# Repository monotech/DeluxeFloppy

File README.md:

Monotech DeluxeFloppy
----

Schematic is based on Sergey Kiselev's (https://github.com/skiselev) design: http://www.malinov.com/Home/sergeys-projects/isa-fdc-and-uart

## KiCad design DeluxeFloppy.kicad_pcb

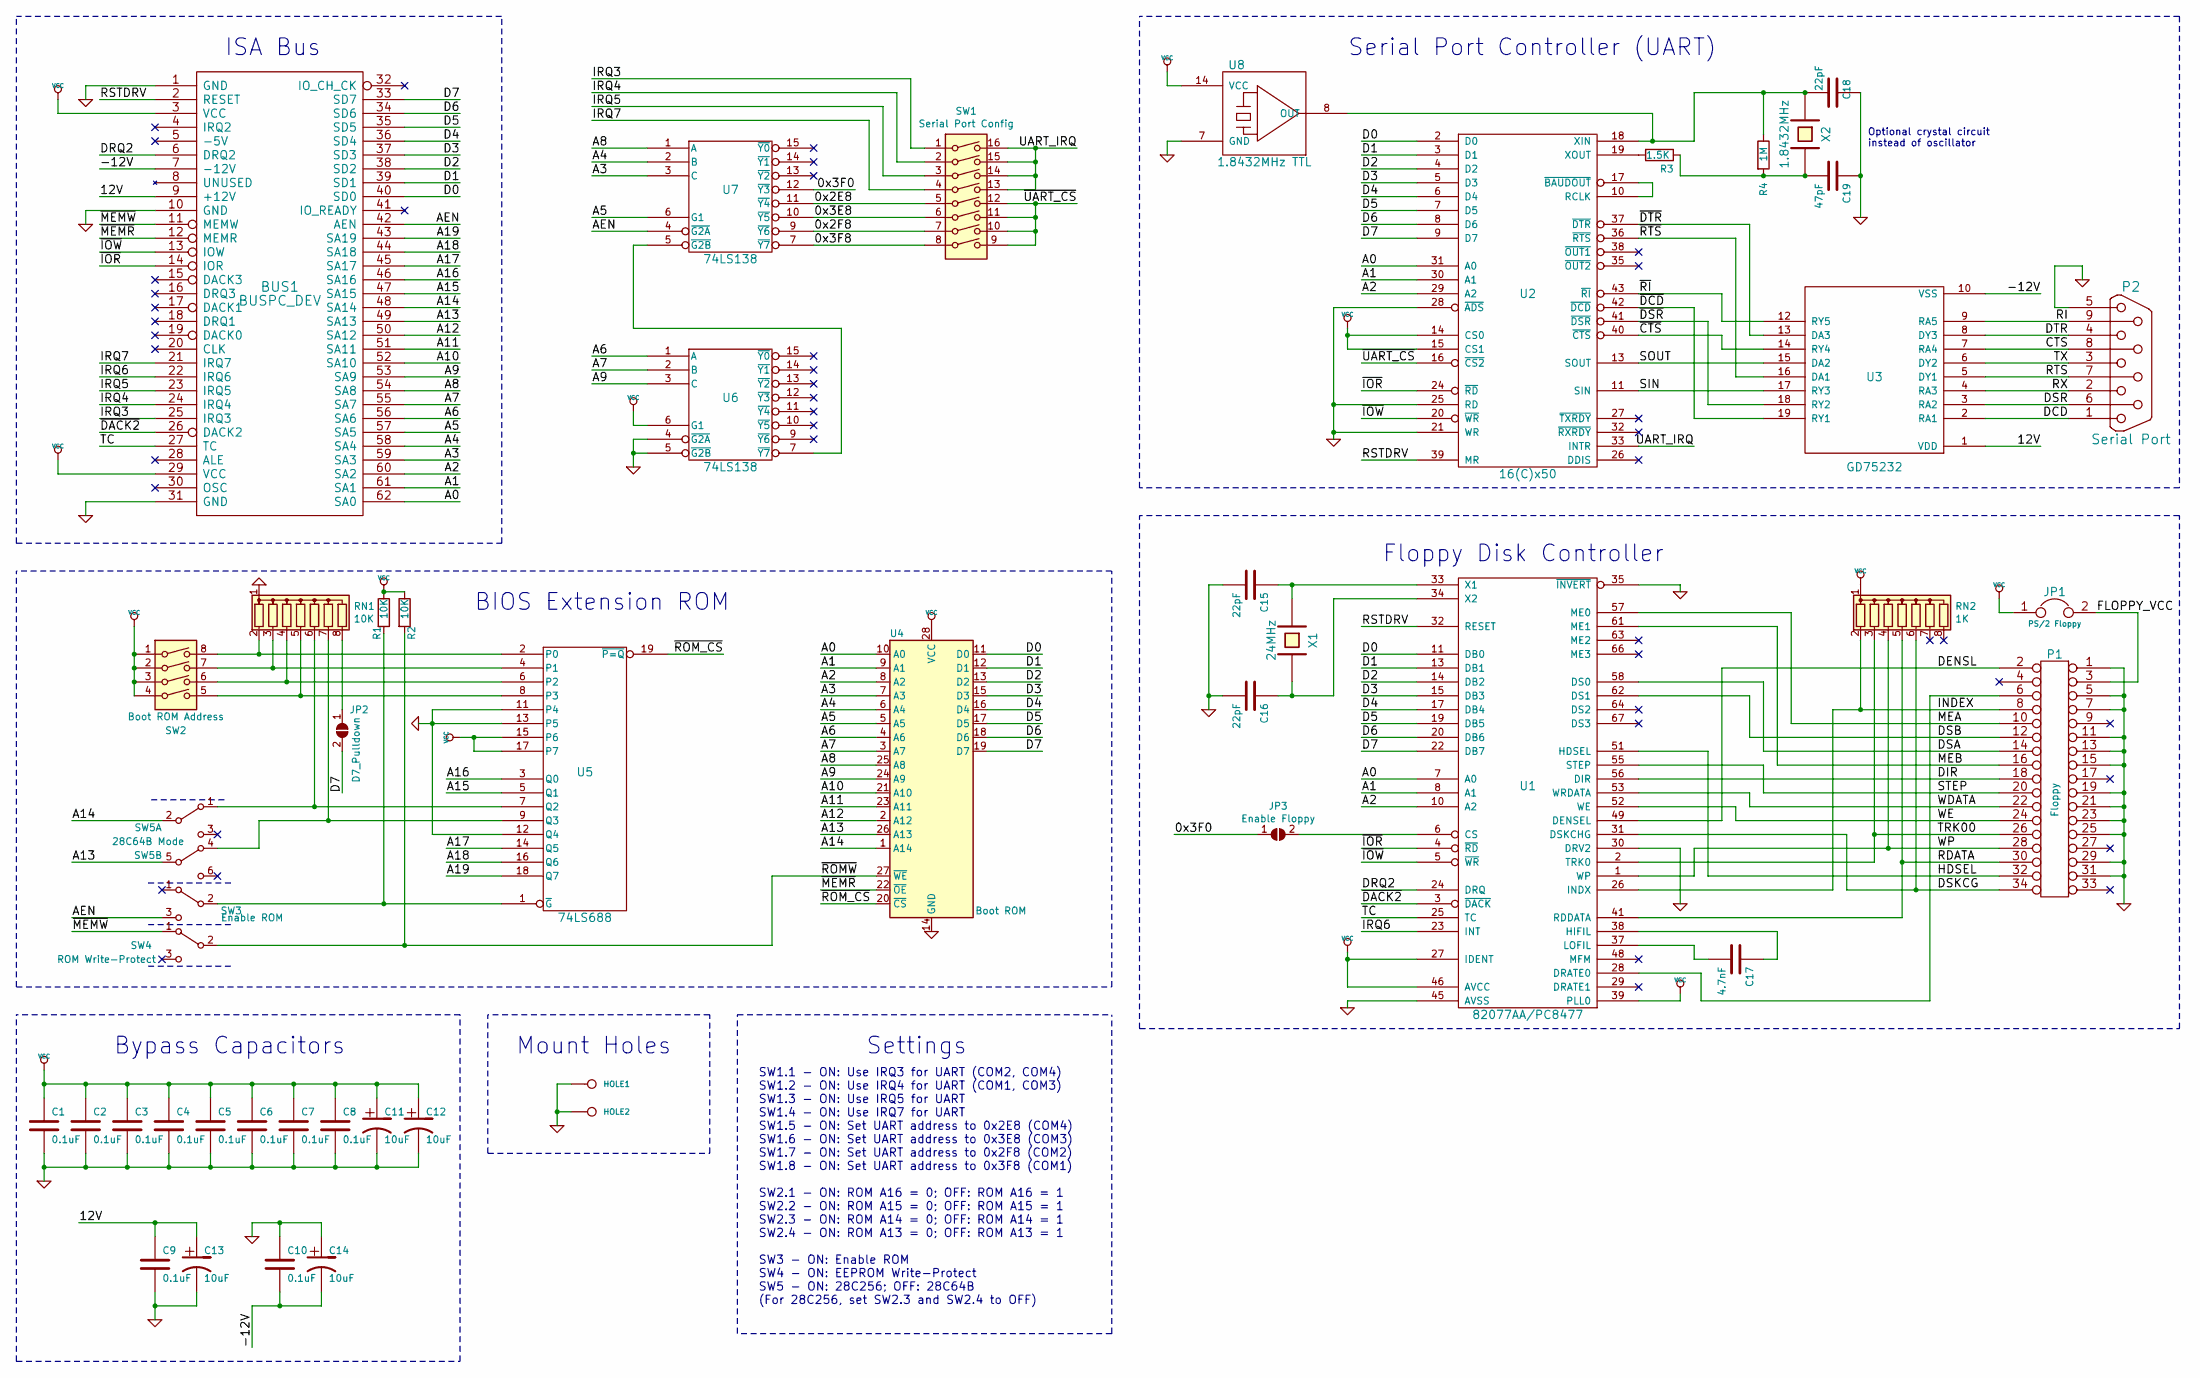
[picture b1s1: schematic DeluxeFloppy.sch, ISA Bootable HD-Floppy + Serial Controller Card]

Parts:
BUS1: BUSPC_DEV; Conn_Bus_ISA8
C1, C2, C3, C4, C5, C6, C7, C8, C9, C10: 0.1uF; C_Disc_D4.3mm_W1.9mm_P5.00mm
C11, C12, C13, C14: 10uF; C_Disc_D4.3mm_W1.9mm_P5.00mm
C15, C16, C18: 22pF; C_Disc_D4.3mm_W1.9mm_P5.00mm
C17: 4.7nF; C_Disc_D4.3mm_W1.9mm_P5.00mm
C19: 47pF; C_Disc_D4.3mm_W1.9mm_P5.00mm
HOLE1, HOLE2: CONN_1; MountingHole_3.2mm_M3_Pad
JP1: PS/2 Floppy; PinHeader_1x02_P2.54mm_Vertical
JP2: D7_Pulldown; SolderJumper-2_P1.3mm_Open_RoundedPad1.0x1.5mm
JP3: Enable Floppy; SolderJumper-2_P1.3mm_Open_RoundedPad1.0x1.5mm
P1: Floppy; Pin_Header_Straight_2x17_Pitch2.54mm_shrouded
P2: Serial Port; Conn_Dsub_DE9M
R1, R2: 10K; R_Axial_DIN0207_L6.3mm_D2.5mm_P7.62mm_Horizontal
R3: 1.5K; R_Axial_DIN0207_L6.3mm_D2.5mm_P7.62mm_Horizontal
R4: 1M; R_Axial_DIN0207_L6.3mm_D2.5mm_P7.62mm_Horizontal
RN1: 10K; R_Array_SIP8
RN2: 1K; R_Array_SIP8
SW1: Serial Port Config; SW_DIP_SPSTx08_Slide_9.78x22.5mm_W7.62mm_P2.54mm
SW2: Boot ROM Address; SW_DIP_SPSTx04_Slide_9.78x12.34mm_W7.62mm_P2.54mm
SW3: Enable ROM; SW_CuK_OS102011MA1QN1_SPDT_Angled
SW4: ROM Write-Protect; SW_CuK_OS102011MA1QN1_SPDT_Angled
SW5: 28C64B Mode; SW_MS-22D18G2
U1: 82077AA/PC8477; PLCC-68_THT-Socket
U2: 16(C)x50; PLCC-44_THT-Socket
U3: GD75232; SSOP-20_5.3x7.2mm_P0.65mm
U4: Boot ROM; DIP-28_W15.24mm_Socket
U5: 74LS688; DIP-20_W7.62mm
U6, U7: 74LS138; DIP-16_W7.62mm
U8: 1.8432MHz TTL; Oscillator_DIP-14
X1: 24MHz; Crystal_HC49-4H_Vertical
X2: 1.8432MHz; Crystal_HC49-U_Horizontal_1EP_style2

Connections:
/0x2E8: SW1.5, U7.11 (~Y4)
/0x2F8: SW1.7, U7.9 (~Y6)
/0x3E8: SW1.6, U7.10 (~Y5)
/0x3F0: JP3.1 (A), U7.12 (~Y3)
/0x3F8: SW1.8, U7.7 (~Y7)
/12V: BUS1.9 (+12V), C9.1, C13.1, U3.1 (VDD)
/-12V: BUS1.7 (-12V), C10.2, C14.2, U3.10 (VSS)
/A0: BUS1.62 (SA0), U1.7 (A0), U2.31 (A0), U4.10 (A0)
/A1: BUS1.61 (SA1), U1.8 (A1), U2.30 (A1), U4.9 (A1)
/A2: BUS1.60 (SA2), U1.10 (A2), U2.29 (A2), U4.8 (A2)
/A3: BUS1.59 (SA3), U4.7 (A3), U7.3 (C)
/A4: BUS1.58 (SA4), U4.6 (A4), U7.2 (B)
/A5: BUS1.57 (SA5), U4.5 (A5), U7.6 (G1)
/A6: BUS1.56 (SA6), U4.4 (A6), U6.1 (A)
/A7: BUS1.55 (SA7), U4.3 (A7), U6.2 (B)
/A8: BUS1.54 (SA8), U4.25 (A8), U7.1 (A)
/A9: BUS1.53 (SA9), U4.24 (A9), U6.3 (C)
/A10: BUS1.52 (SA10), U4.21 (A10)
/A11: BUS1.51 (SA11), U4.23 (A11)
/A12: BUS1.50 (SA12), U4.2 (A12)
/A13: BUS1.49 (SA13), SW5.5 (B), U4.26 (A13)
/A14: BUS1.48 (SA14), SW5.2 (B), U4.1 (A14)
/A15: BUS1.47 (SA15), U5.5 (Q1)
/A16: BUS1.46 (SA16), U5.3 (Q0)
/A17: BUS1.45 (SA17), U5.14 (Q5)
/A18: BUS1.44 (SA18), U5.16 (Q6)
/A19: BUS1.43 (SA19), U5.18 (Q7)
/AEN: BUS1.42 (AEN), SW3.3 (C), U7.4 (~G2A)
/CTS: P2.8, U3.7 (RA4)
/D0: BUS1.40 (SD0), U1.11 (DB0), U2.2 (D0), U4.11 (D0)
/D1: BUS1.39 (SD1), U1.13 (DB1), U2.3 (D1), U4.12 (D1)
/D2: BUS1.38 (SD2), U1.14 (DB2), U2.4 (D2), U4.13 (D2)
/D3: BUS1.37 (SD3), U1.15 (DB3), U2.5 (D3), U4.15 (D3)
/D4: BUS1.36 (SD4), U1.17 (DB4), U2.6 (D4), U4.16 (D4)
/D5: BUS1.35 (SD5), U1.19 (DB5), U2.7 (D5), U4.17 (D5)
/D6: BUS1.34 (SD6), U1.20 (DB6), U2.8 (D6), U4.18 (D6)
/D7: BUS1.33 (SD7), JP2.2 (B), U1.22 (DB7), U2.9 (D7), U4.19 (D7)
/DCD: P2.1, U3.2 (RA1)
/DENSL: P1.2, U1.49 (DENSEL)
/DIR: P1.18, U1.56 (DIR)
/DRQ2: BUS1.6 (DRQ2), U1.24 (DRQ)
/DSA: P1.14, U1.58 (DS0)
/DSB: P1.12, U1.62 (DS1)
/DSKCG: P1.34, RN2.6 (R5), U1.31 (DSKCHG)
/DSR: P2.6, U3.3 (RA2)
/DTR: P2.4, U3.8 (DY3)
/FLOPPY_VCC: JP1.2, P1.3
/HDSEL: P1.32, U1.51 (HDSEL)
/INDEX: P1.8, RN2.2 (R1), U1.26 (INDX)
/IRQ3: BUS1.25 (IRQ3), SW1.1
/IRQ4: BUS1.24 (IRQ4), SW1.2
/IRQ5: BUS1.23 (IRQ5), SW1.3
/IRQ6: BUS1.22 (IRQ6), U1.23 (INT)
/IRQ7: BUS1.21 (IRQ7), SW1.4
/MEA: P1.10, U1.57 (ME0)
/MEB: P1.16, U1.61 (ME1)
/RDATA: P1.30, RN2.5 (R4), U1.41 (RDDATA)
/RI: P2.9, U3.9 (RA5)
/RSTDRV: BUS1.2 (RESET), U1.32 (RESET), U2.39 (MR)
/RTS: P2.7, U3.5 (DY1)
/RX: P2.2, U3.4 (RA3)
/SIN: U2.11 (SIN), U3.17 (RY3)
/SOUT: U2.13 (SOUT), U3.15 (DA2)
/STEP: P1.20, U1.55 (STEP)
/TC: BUS1.27 (TC), U1.25 (TC)
/TRK00: P1.26, RN2.3 (R2), U1.2 (TRK0)
/TX: P2.3, U3.6 (DY2)
/UART_IRQ: SW1.13, SW1.14, SW1.15, SW1.16, U2.33 (INTR)
/WDATA: P1.22, U1.53 (WRDATA)
/WE: P1.24, U1.52 (WE)
/WP: P1.28, RN2.4 (R3), U1.1 (WP)
/~CTS: U2.40 (~CTS), U3.14 (RY4)
/~DACK2: BUS1.26 (DACK2), U1.3 (~DACK)
/~DCD: U2.42 (~DCD), U3.19 (RY1)
/~DSR: U2.41 (~DSR), U3.18 (RY2)
/~DTR: U2.37 (~DTR), U3.13 (DA3)
/~IOR: BUS1.14 (IOR), U1.4 (~RD), U2.24 (~RD)
/~IOW: BUS1.13 (IOW), U1.5 (~WR), U2.20 (~WR)
/~MEMR: BUS1.12 (MEMR), U4.22 (~OE)
/~MEMW: BUS1.11 (MEMW), SW4.1 (A)
/~RI: U2.43 (~RI), U3.12 (RY5)
/~ROMW: R2.2, SW4.2 (B), U4.27 (~WE)
/~ROM_CS: U4.20 (~CS), U5.19 (~P=Q)
/~RTS: U2.36 (~RTS), U3.16 (DA1)
/~UART_CS: SW1.9, SW1.10, SW1.11, SW1.12, U2.16 (~CS2)
GND: BUS1.1 (GND), BUS1.10 (GND), BUS1.31 (GND), C1.2, C2.2, C3.2, C4.2, C5.2, C6.2, C7.2, C8.2, C9.2, C10.1, C11.2, C12.2, C13.2, C14.1, C15.2, C16.2, C18.1, C19.1, HOLE1.1, HOLE2.1, P1.1, P1.5, P1.7, P1.11, P1.13, P1.15, P1.19, P1.21, P1.23, P1.25, P1.29, P1.31, P2.5, RN1.1 (common), U1.9 (GND), U1.12 (GND), U1.16 (GND), U1.21 (GND), U1.30 (DRV2), U1.35 (~INVERT), U1.36 (GND), U1.45 (AVSS), U1.50 (GND), U1.54 (GND), U1.59 (GND), U1.65 (GND), U2.21 (WR), U2.22 (GND), U2.25 (RD), U2.28 (~ADS), U3.11 (GND), U4.14 (GND), U5.10 (GND), U5.11 (P4), U5.12 (Q4), U5.13 (P5), U6.4 (~G2A), U6.5 (~G2B), U6.8 (GND), U7.8 (GND), U8.7 (GND)
unnamed: C15.1, U1.33 (X1), X1.1
unnamed: C16.1, U1.34 (X2), X1.2
unnamed: C17.1, U1.38 (HIFIL)
unnamed: C17.2, U1.37 (LOFIL)
unnamed: C18.2, R4.1, U2.18 (XIN), U8.8 (OUT), X2.1
unnamed: C19.2, R3.1, R4.2, X2.2
unnamed: JP2.1 (A), RN1.8 (R7)
unnamed: JP3.2 (B), U1.6 (CS)
unnamed: P1.6, U1.28 (DRATE0)
unnamed: R1.2, SW3.2 (B), U5.1 (~G)
unnamed: R3.2, U2.19 (XOUT)
unnamed: RN1.2 (R1), SW2.8, U5.2 (P0)
unnamed: RN1.3 (R2), SW2.7, U5.4 (P1)
unnamed: RN1.4 (R3), SW2.6, U5.6 (P2)
unnamed: RN1.5 (R4), SW2.5, U5.8 (P3)
unnamed: RN1.6 (R5), SW5.1 (A), U5.7 (Q2)
unnamed: RN1.7 (R6), SW5.4 (A), U5.9 (Q3)
unnamed: U2.10 (RCLK), U2.17 (~BAUDOUT)
unnamed: U6.7 (~Y7), U7.5 (~G2B)
VCC: BUS1.3 (VCC), BUS1.29 (VCC), C1.1, C2.1, C3.1, C4.1, C5.1, C6.1, C7.1, C8.1, C11.1, C12.1, JP1.1, R1.1, R2.1, RN2.1 (common), SW2.1, SW2.2, SW2.3, SW2.4, U1.18 (VCC), U1.27 (IDENT), U1.39 (PLL0), U1.40 (VCC), U1.46 (AVCC), U1.60 (VCC), U1.68 (VCC), U2.14 (CS0), U2.15 (CS1), U2.44 (VCC), U3.20 (VCC), U4.28 (VCC), U5.15 (P6), U5.17 (P7), U5.20 (VCC), U6.6 (G1), U6.16 (VCC), U7.16 (VCC), U8.14 (VCC)

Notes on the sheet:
ISA Bus
BIOS Extension ROM
Bypass Capacitors
Mount Holes
Serial Port Controller (UART)
Floppy Disk Controller
SW1.1 - ON: Use IRQ3 for UART (COM2, COM4) SW1.2 - ON: Use IRQ4 for UART (COM1, COM3) SW1.3 - ON: Use IRQ5 for UART SW1.4 - ON: Use IRQ7 for UART SW1.5 - ON: Set UART address to 0x2E8 (COM4) SW1.6 - ON: Set UART address to 0x3E8 (COM3) SW1.7 - ON: Set UART address to 0x2F8 (COM2) SW1.8 - ON: Set UA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
Settings
Optional crystal circuit instead of oscillator

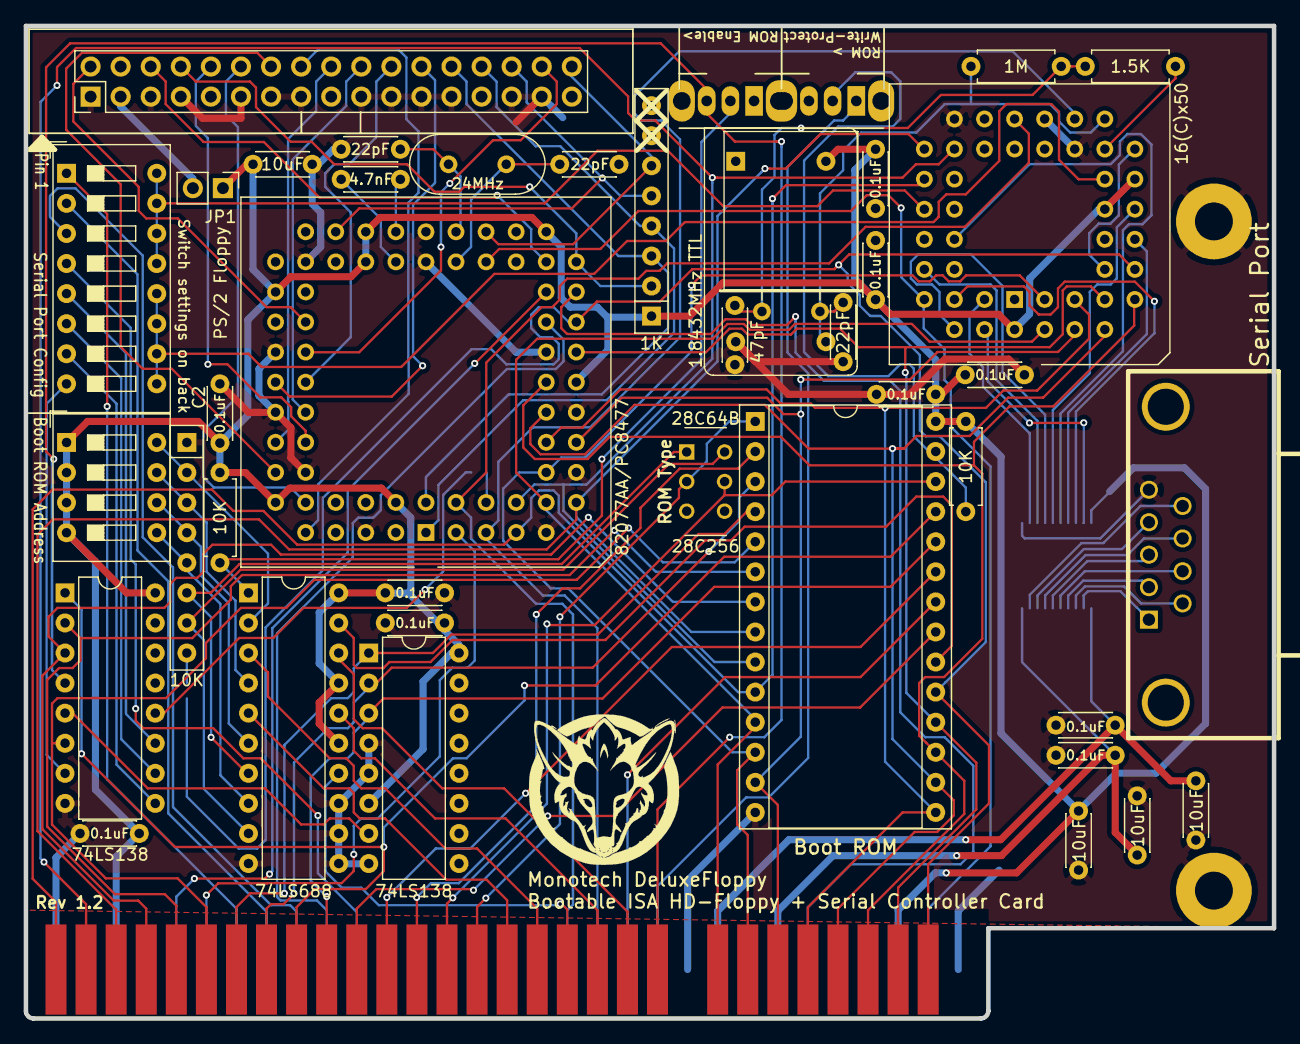
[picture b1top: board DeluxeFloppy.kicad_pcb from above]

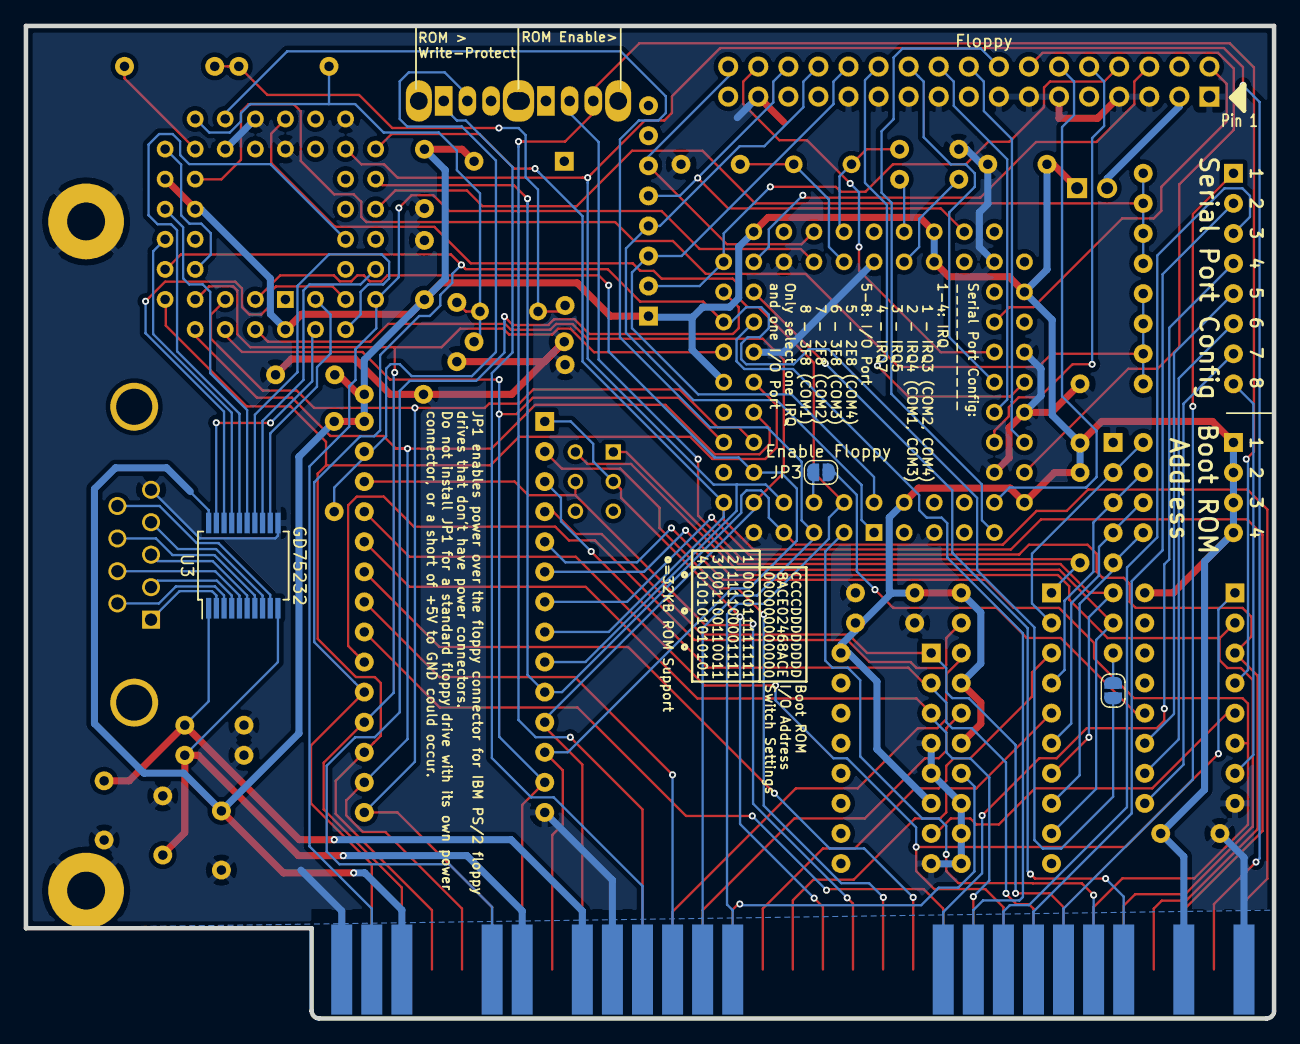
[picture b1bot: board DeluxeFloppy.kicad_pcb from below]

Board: 2 copper layers, 105.4 x 83.8 mm, 48 parts (3 on the bottom side), 106 nets.

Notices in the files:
DeluxeFloppy.kicad_pcb:
GPL v3
